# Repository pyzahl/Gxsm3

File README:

General Information
===================

GXSM -- Gnome X Scanning Microscopy: A multi-channel image and
vector-probe data acquisition and visualization system designed for
SPM techniques (STM,AFM..), but also SPA-LEED. A plug-in interface
allows any user add-on data-processing and special hardware and
instrument support.

Based on several hardware options it supports a commercially available
DSP hardware and provided also Open Source Code for all the low level
signal processing tasks and instrument controls in a most flexible and
adaptable manner.

All latest stable software is available
via SVN (gxsm2) and GIT (gxsm3-beta) only

or Live Demo/Install CD:
http://www.ventiotec.de/linux/GXSM-Linux.iso

GXSM Web Site: http://gxsm.sf.net

Installation
============

gxsm3 requires GTK+ >= 3.14.0, GtkSourceView >= 3.14.0, libfftw, libnetcdf, libquicktime
and PyGobject 3.0.x are required to enable python / scripting support.

Simple install procedure:

  % git clone ... gxsm3-src			# checkout / unpack the sources
  % cd gxsm3-src				# change to the toplevel directory
  % ./autogen.sh				# run the `autogen' script
  % make					# build gedit
  [ Become root if necessary ]
  % make install				# install gxsm3

See the file 'INSTALL' for more detailed information.

How to report bugs
==================

Bugs should be reported to the GNOME bug tracking system.
(http://bugzilla.gnome.org, product gedit). You will need to create an
account for yourself.

In the bug report please include:

* Information about your system. For instance:

   - What version of gxsm3
   - What operating system and version
   - What version of the gtk+, glib and gnome libraries

  And anything else you think is relevant.

* How to reproduce the bug. 

* If the bug was a crash, the exact text that was printed out when the
  crash occurred.

* Further information such as stack traces may be useful, but is not
  necessary. If you do send a stack trace, and the error is an X error,
  it will be more useful if the stack trace is produced running the test
  program with the --sync command line option.

Patches
=======

Patches should also be submitted to bugzilla.gnome.org. If the patch
fixes an existing bug, add the patch as an attachment to that bug
report.

Otherwise, enter a new bug report that describes the patch, and attach
the patch to that bug report.

Please create patches with the git format-patch command.

If you are interested in helping us to develop gedit, please see the 
file 'AUTHOR' for contact information and/or send a message to the gedit
mailing list. See also the file 'HACKING' for more detailed information.

  The gxsm team.

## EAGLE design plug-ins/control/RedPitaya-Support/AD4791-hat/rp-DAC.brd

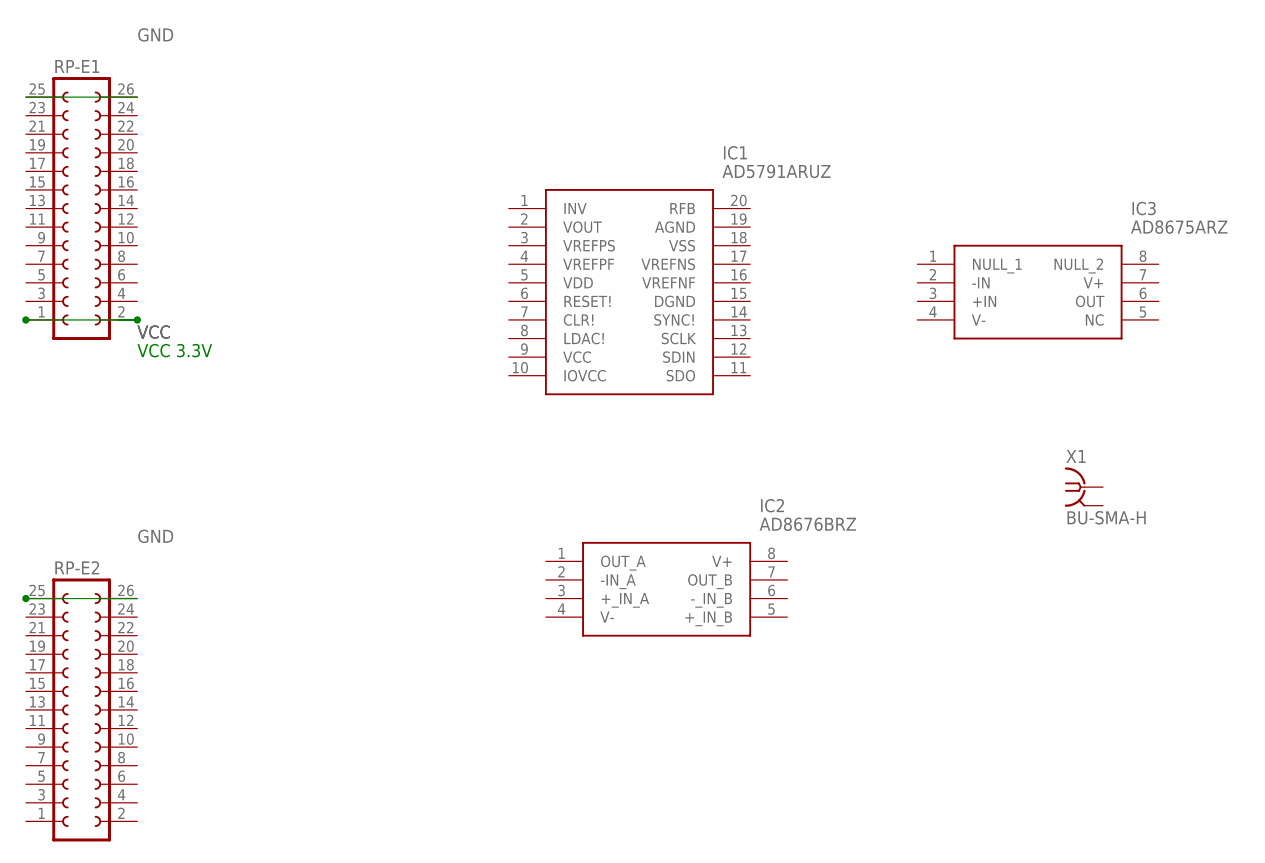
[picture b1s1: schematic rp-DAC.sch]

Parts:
IC1: AD5791ARUZ; SOP65P640X120-20N
IC2: AD8676BRZ; SOIC127P600X175-8N
IC3: AD8675ARZ; SOIC127P600X175-8N
RP-E1, RP-E2: FE13-2
X1: BU-SMA-H

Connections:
GND: RP-E1.25, RP-E1.26, RP-E2.25, RP-E2.26
VCC: RP-E1.1, RP-E1.2

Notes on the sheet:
VCC 3.3V

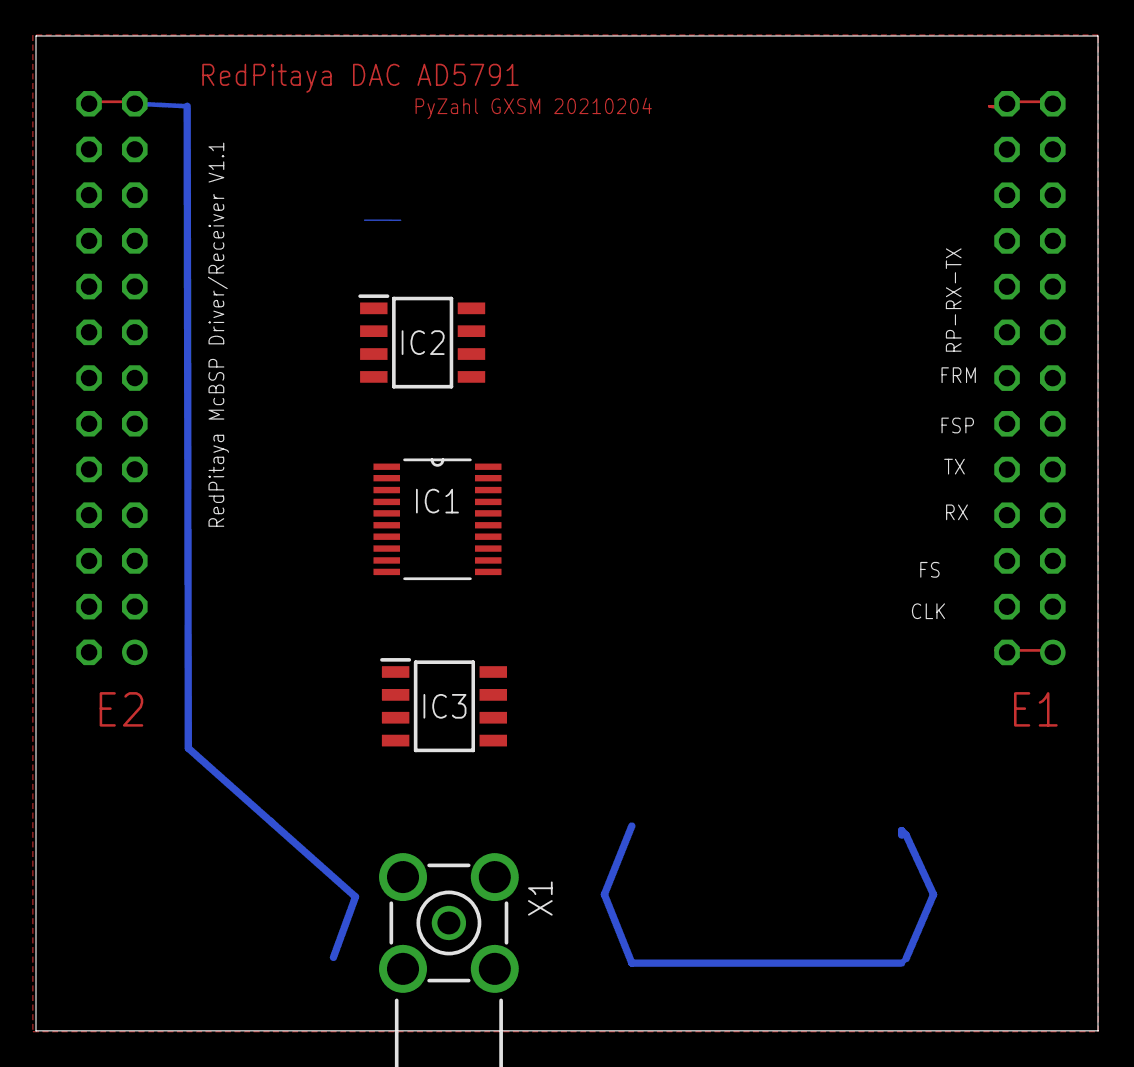
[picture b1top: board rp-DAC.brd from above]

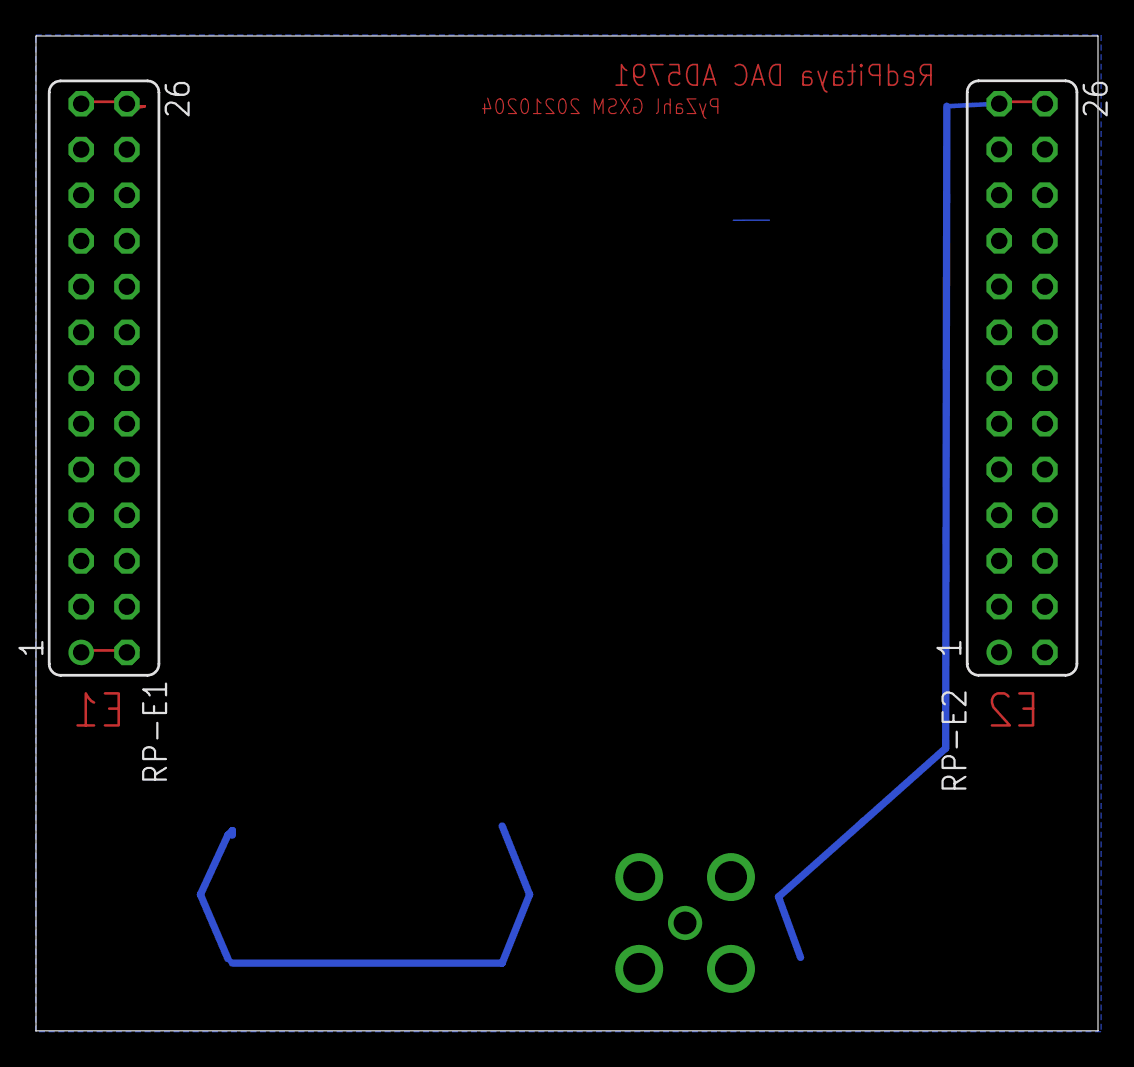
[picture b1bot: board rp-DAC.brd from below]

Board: 2 copper layers, 59.0 x 55.3 mm, 6 parts (2 on the bottom side), 2 nets.

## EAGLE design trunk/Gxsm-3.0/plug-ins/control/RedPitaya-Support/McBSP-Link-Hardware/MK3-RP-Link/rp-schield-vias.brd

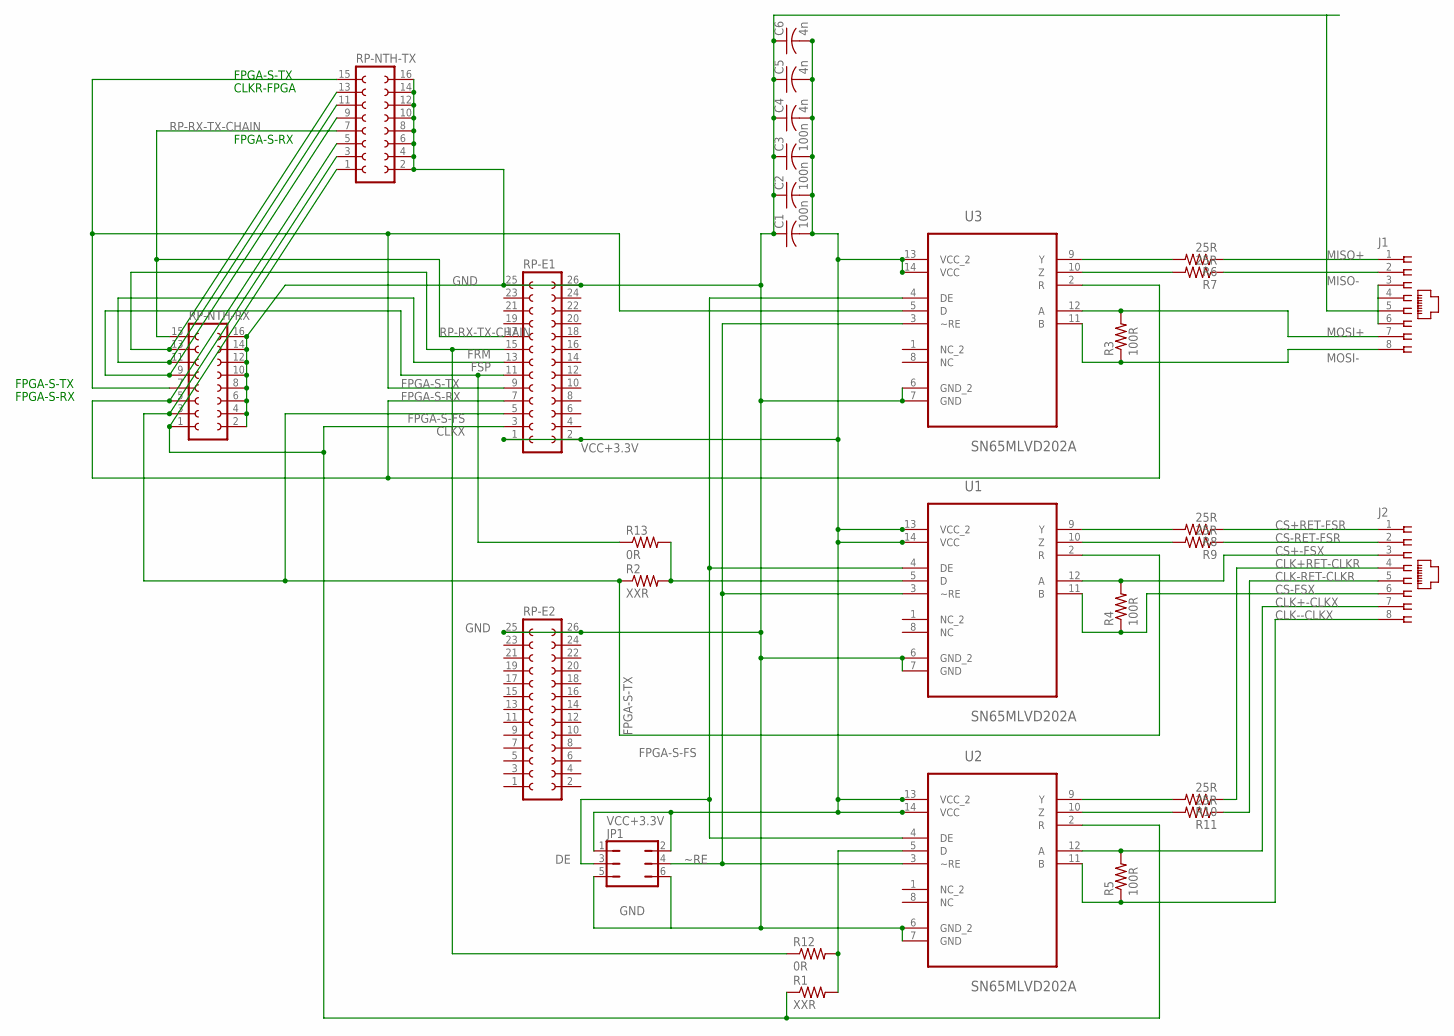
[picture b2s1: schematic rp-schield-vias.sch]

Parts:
C1, C2, C3: 100n; C0805
C4, C5, C6: 4n; C0805
J1, J2: 557785-1-SHIELD; 557785-1
JP1: JP3Q
R1, R2: XXR; M1206
R3, R4, R5: 100R; R0402
R6, R7, R8, R9, R10, R11: 25R; R0402
R12, R13: 0R; M1206
RP-E1, RP-E2: FE13-2
RP-NTH-RX: FE08-2
RP-NTH-TX: FE08-2
U1, U2, U3: SN65MLVD202A; SOIC127P600X175-14N

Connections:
CLK+-CLKX: J2.4, R10.1
CLK+RET-CLKR: J2.7, R5.2, U2.12 (A)
CLK--CLKX: J2.5, R11.1
CLK-RET-CLKR: J2.8, R5.1, U2.11 (B)
CLKX: R1.1, RP-E1.3, RP-NTH-RX.1, RP-NTH-TX.1, U2.2 (R)
CS+-FSX: J2.3, R4.2, U1.12 (A)
CS+RET-FSR: J2.1, R8.1
CS-FSX: J2.6, R4.1, U1.11 (B)
CS-RET-FSR: J2.2, R9.1
DE: JP1.3, U1.4 (DE), U2.4 (DE), U3.4 (DE)
FPGA-S-FS: R2.1, RP-E1.5, RP-NTH-RX.3, RP-NTH-TX.3, U1.2 (R)
FPGA-S-RX: RP-E1.7, RP-NTH-RX.5, RP-NTH-TX.5, U3.2 (R)
FPGA-S-TX: RP-E1.9, RP-NTH-RX.7, RP-NTH-TX.15, U3.5 (D)
FRM: RP-E1.13, RP-NTH-RX.11, RP-NTH-TX.11
FSP: R13.1, RP-E1.11, RP-NTH-RX.9, RP-NTH-TX.9
GND: C1.1, C2.1, C3.1, C4.1, C5.1, C6.1, J1.3, J1.4, J1.5, J1.6, JP1.5, JP1.6, RP-E1.25, RP-E1.26, RP-E2.25, RP-E2.26, RP-NTH-RX.2, RP-NTH-RX.4, RP-NTH-RX.6, RP-NTH-RX.8, RP-NTH-RX.10, RP-NTH-RX.12, RP-NTH-RX.14, RP-NTH-RX.16, RP-NTH-TX.2, RP-NTH-TX.4, RP-NTH-TX.6, RP-NTH-TX.8, RP-NTH-TX.10, RP-NTH-TX.12, RP-NTH-TX.14, RP-NTH-TX.16, U1.6 (GND_2), U1.7 (GND), U2.6 (GND_2), U2.7 (GND), U3.6 (GND_2), U3.7 (GND)
MISO+: J1.1, R6.1
MISO-: J1.2, R7.1
MOSI+: J1.7, R3.2, U3.12 (A)
MOSI-: J1.8, R3.1, U3.11 (B)
unnamed: R6.2, U3.9 (Y)
unnamed: R1.2, R12.2, U2.5 (D)
unnamed: R7.2, U3.10 (Z)
unnamed: R8.2, U1.9 (Y)
unnamed: R9.2, U1.10 (Z)
unnamed: R2.2, R13.2, U1.5 (D)
unnamed: R10.2, U2.9 (Y)
unnamed: R11.2, U2.10 (Z)
unnamed: R12.1, RP-E1.15, RP-NTH-RX.13, RP-NTH-TX.13
RP-RX-TX-CHAIN: RP-E1.17, RP-NTH-RX.15, RP-NTH-TX.7
VCC+3.3V: C1.2, C2.2, C3.2, C4.2, C5.2, C6.2, JP1.1, JP1.2, RP-E1.1, RP-E1.2, U1.13 (VCC_2), U1.14 (VCC), U2.13 (VCC_2), U2.14 (VCC), U3.13 (VCC_2), U3.14 (VCC)
~RE: JP1.4, U1.3 (~RE), U2.3 (~RE), U3.3 (~RE)

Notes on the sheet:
FPGA-S-TX
FPGA-S-RX
CLKR-FPGA

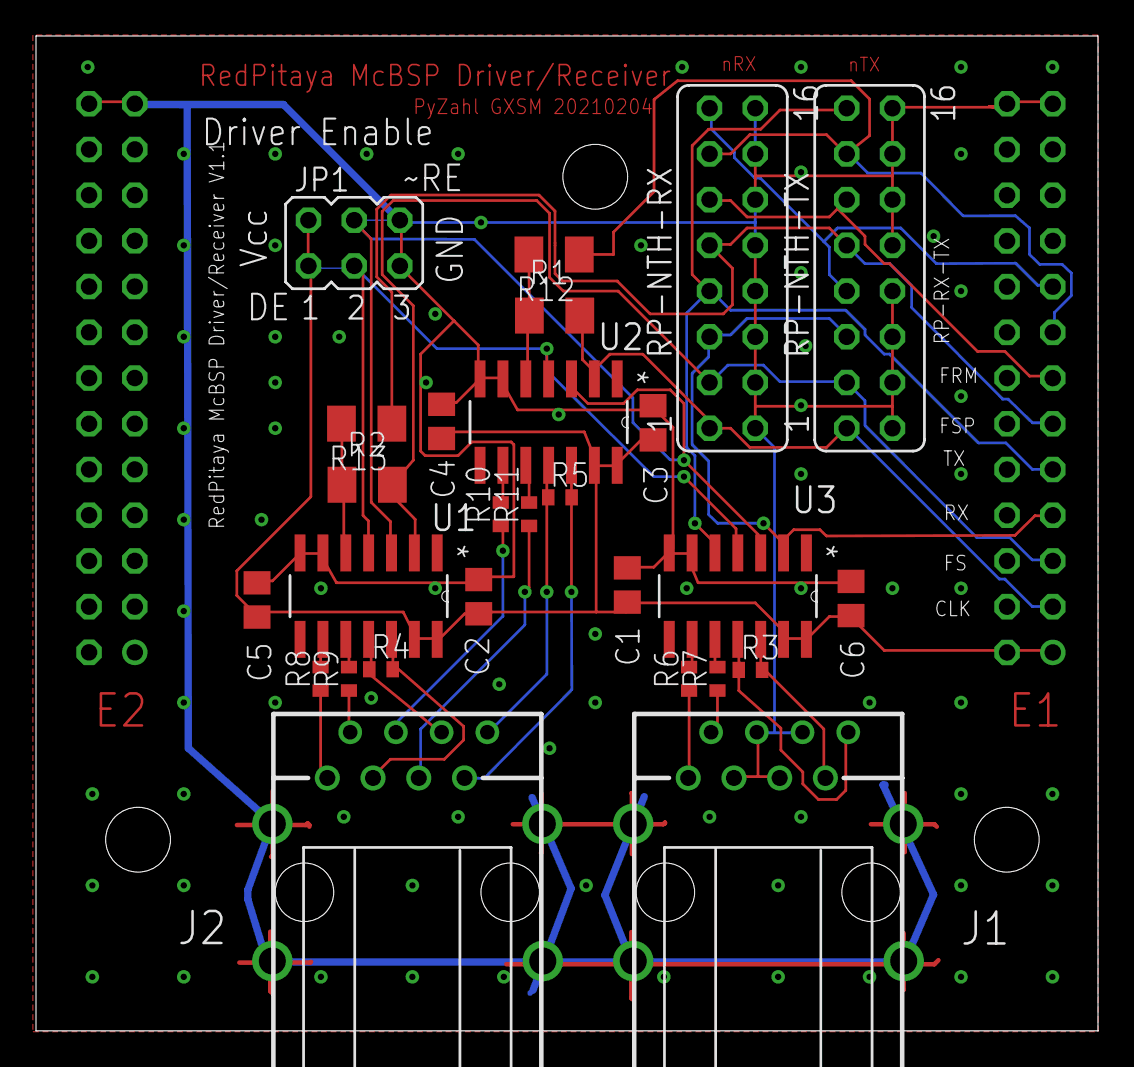
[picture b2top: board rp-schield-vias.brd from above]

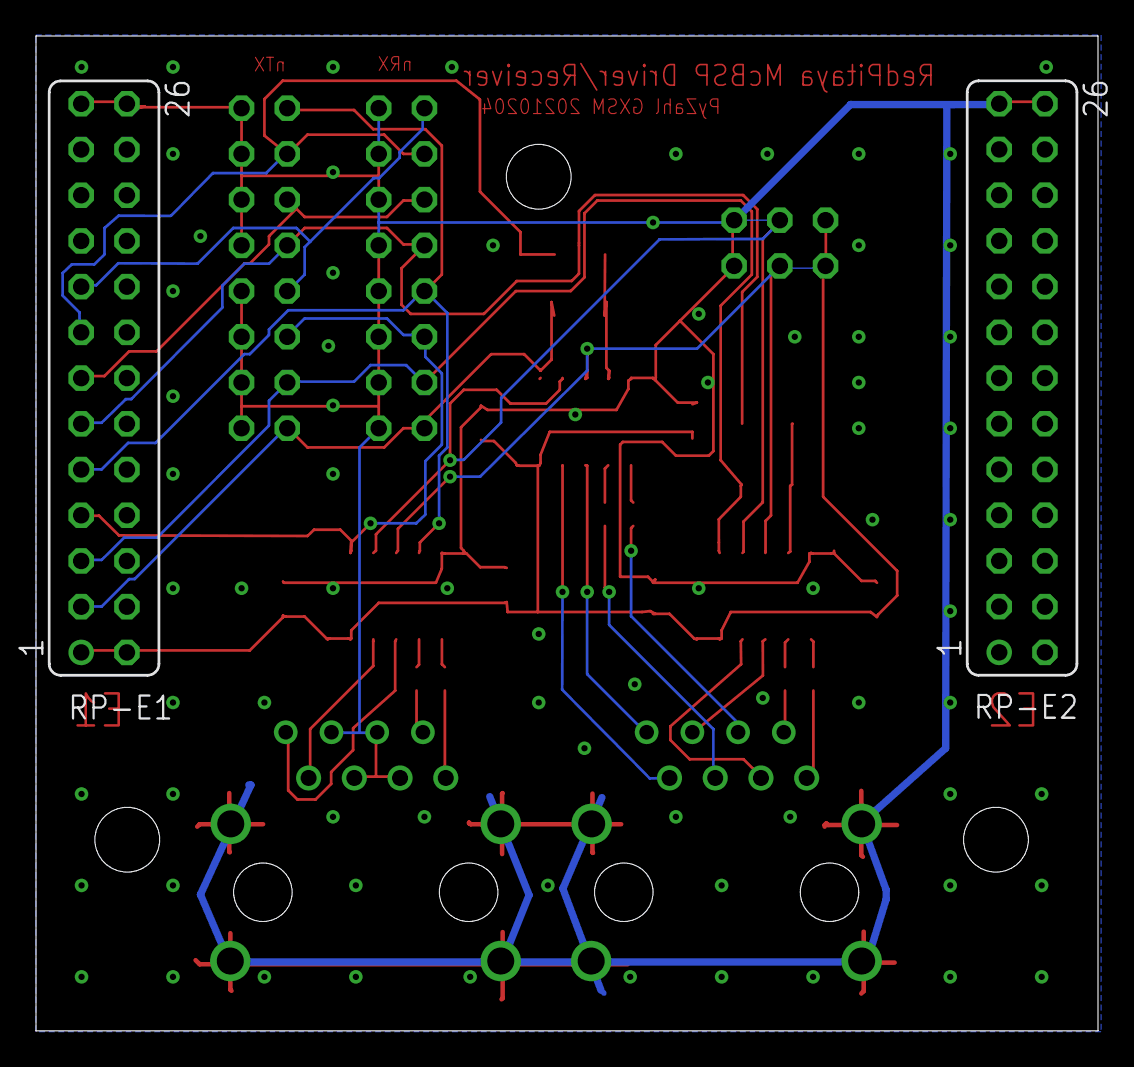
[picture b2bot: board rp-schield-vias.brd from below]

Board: 2 copper layers, 59.0 x 55.3 mm, 29 parts (2 on the bottom side), 32 nets.

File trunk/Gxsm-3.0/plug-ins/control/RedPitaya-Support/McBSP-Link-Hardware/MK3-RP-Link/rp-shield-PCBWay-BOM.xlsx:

Percy Zahl, GXSM RP PACPLL Interface Project |  |  | RP-SHIELD BOM (Bill of Materials) PCB: 60x56mm |  |  | Date: 20210205
Item # | *Designator | *Qty | Manufacturer | *Mfg Part # | Description / Value | *Package/Footprint | Type | Your Instructions / Notes
1 | U1, U2, U3 | 3 | Texas Instruments | SN65MLVD202ADR | SN65MLVD202A Full-duplex M-LVDS transceiver with improved ESD | SOIC127P600X175-14N | SMD
2 | R1, R2 | 2 | Yaego | RC1206FR-0724R9L | RES SMD 24.9 Ohm 1& 1/4W 1206 (or similar) | 1206 | SMD
3 | C1, C2, C3 | 3 | Yageo | CC0805ZRY5V9BB104 | 0.1µF -20%, +80% 50V Ceramic Capacitor Y5V (F) 0805 (or any 100nF CER >35V) | C0805 | SMD
4 | C4, C5, C6 | 3 | Yageo | CC0805KRX7R9BB392 | 3900pF ±10% 50V Ceramic Capacitor X7R 0805 (or any 4nF CER >35V) | C0805 | SMD
5 | J1,J2 | 2 | Amphenol ICC (FCI) | 95672-001LF | Jack Modular Connector 8p8c (RJ45, Ethernet) 90° Angle (Right) Shielded Cat5 | RJ45 8p8c | Through Hole
6 | JP1 | 0 | - | - | 2x3 jumper | - | Through Hole | do not populate (development/testing only)
7 | RP-E1,RP-E2 | 0 | Adafruit Industries LLC | 1979 [1528-1783-ND (DigiKey)] | 2x13 (26pin) RP connector (raspberry pi style stacking header, long) BOTTOM MOU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 | - | Through Hole | do not populate (BOTTOM MOUNT)
8 | RP-NTH-RX | 0 | - | - | header 2x8 | - | Through Hole | do not populate (optional RP interconnect)

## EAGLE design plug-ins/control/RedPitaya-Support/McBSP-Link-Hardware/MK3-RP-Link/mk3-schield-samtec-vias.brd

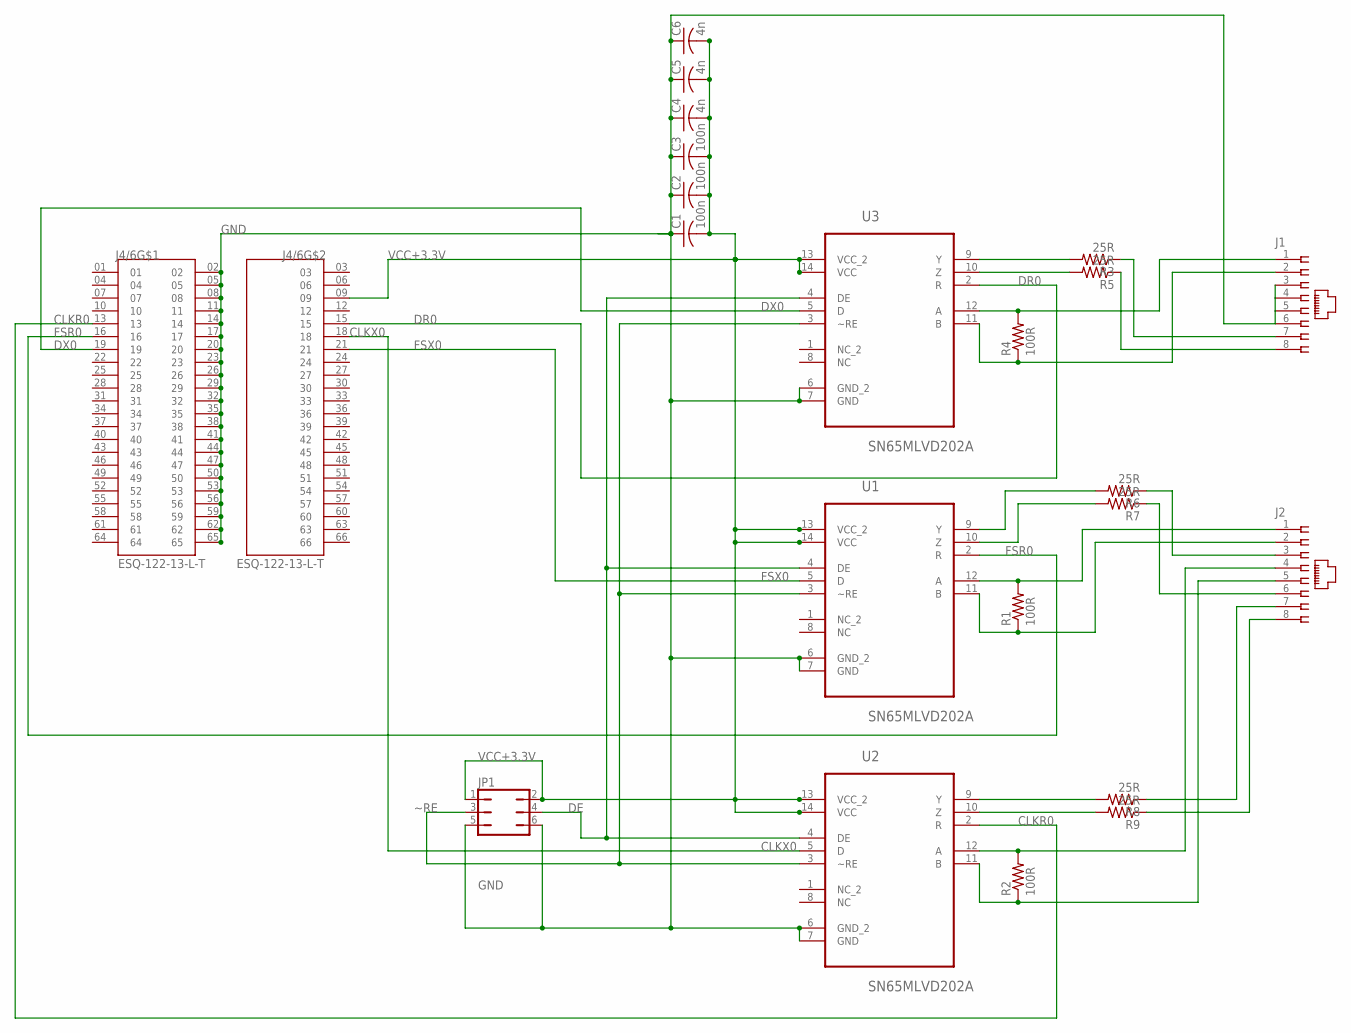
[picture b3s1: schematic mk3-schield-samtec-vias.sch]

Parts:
C1, C2, C3: 100n; C0805
C4, C5, C6: 4n; C0805
J1, J2: 557785-1-SHIELD; 557785-1
J4/6: ESQ-122-13-L-T; SAMTEC_ESQ-122-13-L-T
JP1: JP3Q
R1, R2, R4: 100R; R0402
R3, R5, R6, R7, R8, R9: 25R; R0402
U1, U2, U3: SN65MLVD202A; SOIC127P600X175-14N

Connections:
CLKR0: J4/6.13, U2.2 (R)
CLKX0: J4/6.18, U2.5 (D)
DE: JP1.4, U1.4 (DE), U2.4 (DE), U3.4 (DE)
DR0: J4/6.15, U3.2 (R)
DX0: J4/6.19, U3.5 (D)
FSR0: J4/6.16, U1.2 (R)
FSX0: J4/6.21, U1.5 (D)
GND: C1.1, C2.1, C3.1, C4.1, C5.1, C6.1, J1.3, J1.4, J1.5, J1.6, J4/6.02, J4/6.05, J4/6.08, J4/6.11, J4/6.14, J4/6.17, J4/6.20, J4/6.23, J4/6.26, J4/6.29, J4/6.32, J4/6.35, J4/6.38, J4/6.41, J4/6.44, J4/6.47, J4/6.50, J4/6.53, J4/6.56, J4/6.59, J4/6.62, J4/6.65, JP1.5, JP1.6, U1.6 (GND_2), U1.7 (GND), U2.6 (GND_2), U2.7 (GND), U3.6 (GND_2), U3.7 (GND)
unnamed: J1.1, R4.2, U3.12 (A)
unnamed: J1.2, R4.1, U3.11 (B)
unnamed: J1.7, R3.1
unnamed: J1.8, R5.1
unnamed: J2.1, R1.2, U1.12 (A)
unnamed: J2.2, R1.1, U1.11 (B)
unnamed: J2.3, R6.1
unnamed: J2.6, R7.1
unnamed: J2.4, R2.2, U2.12 (A)
unnamed: J2.5, R2.1, U2.11 (B)
unnamed: J2.7, R8.1
unnamed: J2.8, R9.1
unnamed: R3.2, U3.9 (Y)
unnamed: R5.2, U3.10 (Z)
unnamed: R6.2, U1.9 (Y)
unnamed: R7.2, U1.10 (Z)
unnamed: R8.2, U2.9 (Y)
unnamed: R9.2, U2.10 (Z)
VCC+3.3V: C1.2, C2.2, C3.2, C4.2, C5.2, C6.2, J4/6.09, JP1.1, JP1.2, U1.13 (VCC_2), U1.14 (VCC), U2.13 (VCC_2), U2.14 (VCC), U3.13 (VCC_2), U3.14 (VCC)
~RE: JP1.3, U1.3 (~RE), U2.3 (~RE), U3.3 (~RE)

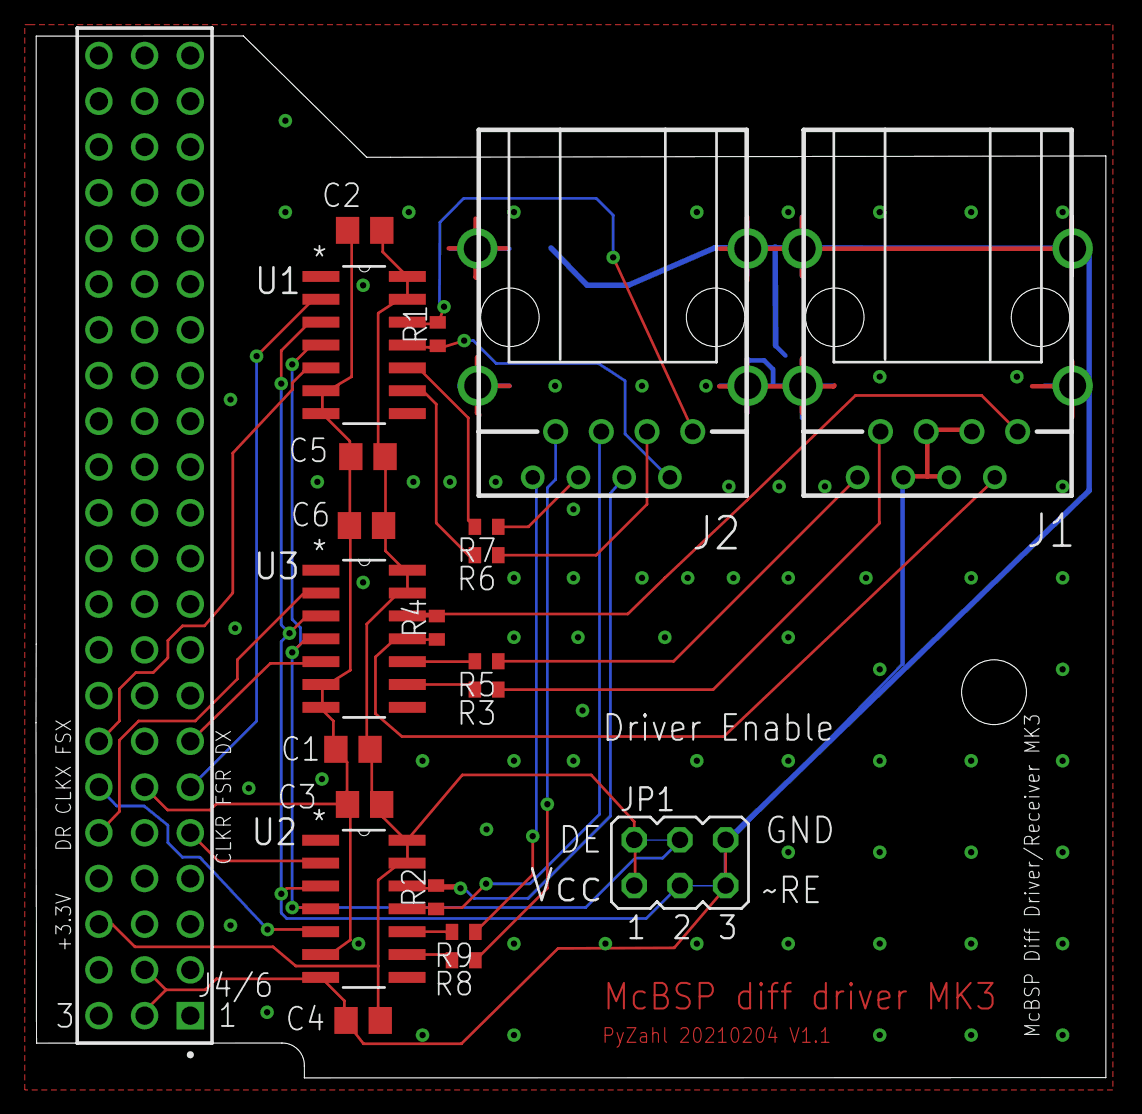
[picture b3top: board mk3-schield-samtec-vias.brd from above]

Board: 2 copper layers, 59.4 x 57.9 mm, 22 parts (0 on the bottom side), 28 nets.

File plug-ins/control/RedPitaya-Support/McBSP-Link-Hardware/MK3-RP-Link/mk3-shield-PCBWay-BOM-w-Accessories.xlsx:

Percy Zahl, GXSM RP PACPLL Interface Project |  |  | MK3-SHIELD BOM (Bill of Materials) PCB: 60x52mm |  |  | Date: 20210205
Item # | *Designator | *Qty | Manufacturer | *Mfg Part # | Description / Value | *Package/Footprint | Type | Your Instructions / Notes
1 | U1, U2, U3 | 3 | Texas Instruments | SN65MLVD202ADR | SN65MLVD202A Full-duplex M-LVDS transceiver with improved ESD | SOIC127P600X175-14N | SMD
2 | C1, C2, C3 | 3 | Yageo | CC0805ZRY5V9BB104 | 0.1µF -20%, +80% 50V Ceramic Capacitor Y5V (F) 0805 (or any 100nF CER >35V) | C0805 | SMD
3 | C4, C5, C6 | 3 | Yageo | CC0805KRX7R9BB392 | 3900pF ±10% 50V Ceramic Capacitor X7R 0805 (or any 4nF CER >35V) | C0805 | SMD
4 | J1,J2 | 2 | Amphenol ICC (FCI) | 95672-001LF | Jack Modular Connector 8p8c (RJ45, Ethernet) 90° Angle (Right) Shielded Cat5 | RJ45 8p8c | Through Hole
5 | JP1 | 0 | - | - | 2x3 jumper | - | Through Hole | do not populate (development/testing only)
6 | JP4/6 | 2 | SamTec | ESQ-122-13-L-T | 3row 44pos in two 2x 3x22 ESQ-122-13-L-T stacking board inter connect |  | Through Hole | do not populate
 |  |  | MK3-SHIELD and RP connection accessories
 |  | 2 | HellermannTyton | PCRED5, PCFEL5 | CAT5 Ethernet CABLE MOD 8P8C Plug-Plug 5ft (Red, Yellow) – may use a shielded c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 |  |  | suggested cable set and length for MK3 – RP link cable. Longer works, may limit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
 |  | 2 | Adafruit industries sLLC | 909 [1528-1572-ND (DigiKey)] | Modular Cable Jack to Plug 8p8c (RJ45, Ethernet) 0.98' (300.0mm) |  |  | for MK3 internal wiring to rear panel
 | JP4/6 | 2 | SamTec | ESQ-122-13-L-T | 3row 44pos in two 2x 3x22 ESQ-122-13-L-T stacking board inter connect |  |  | cut pins CLKR0, DR0, FSR0 !!! Should NOT connect to A810.

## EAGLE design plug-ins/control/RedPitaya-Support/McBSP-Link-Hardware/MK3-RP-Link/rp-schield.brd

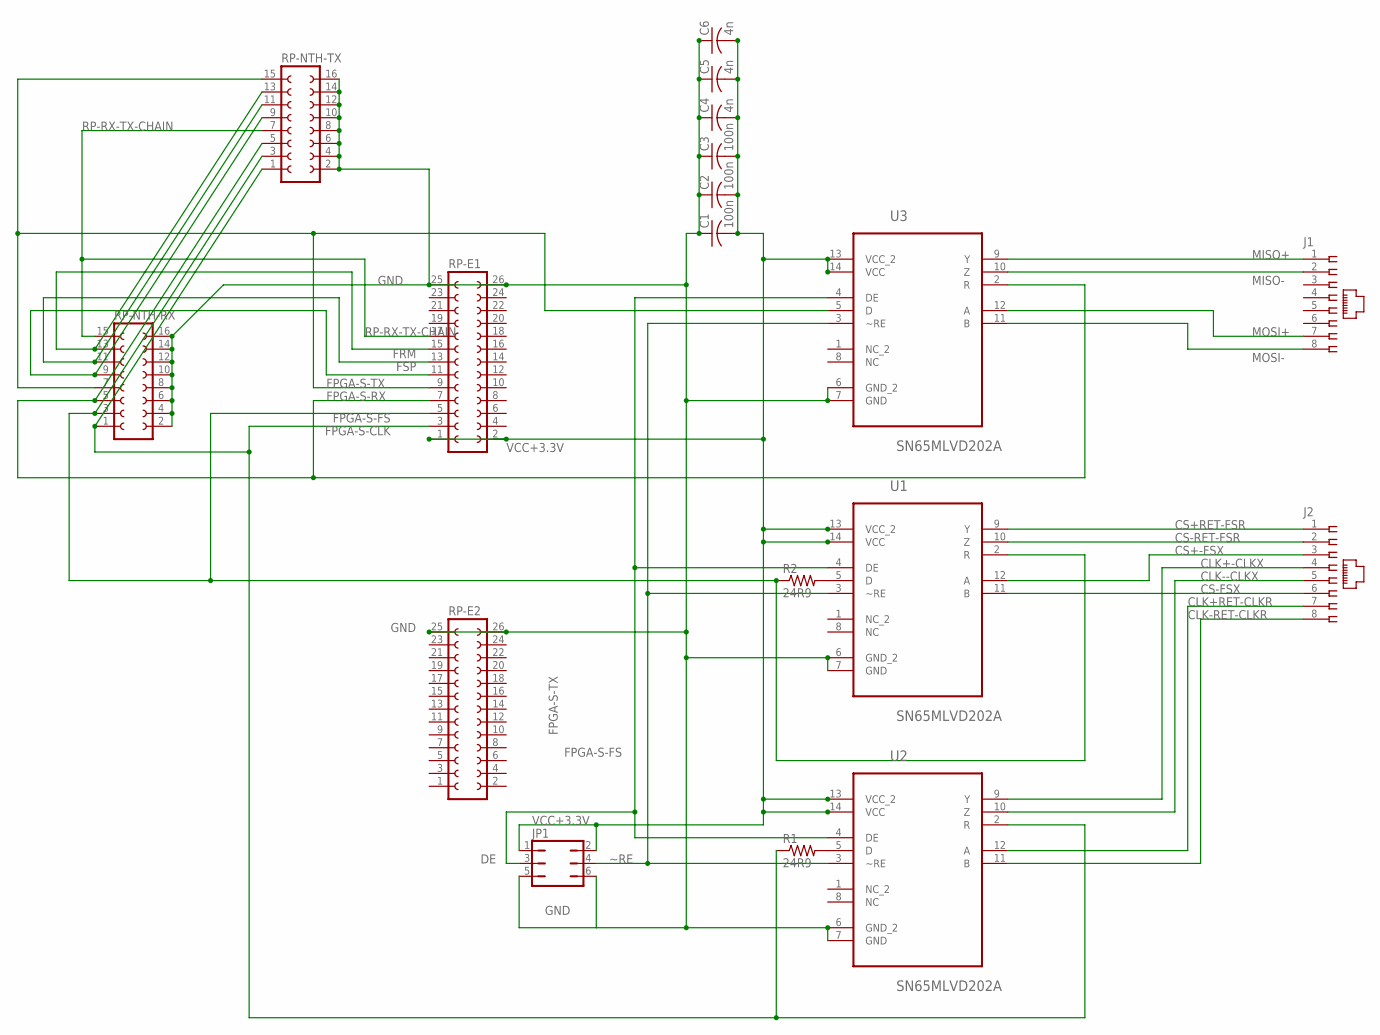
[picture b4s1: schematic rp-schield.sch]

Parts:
C1, C2, C3: 100n; C0805
C4, C5, C6: 4n; C0805
J1, J2: 557785-1-SHIELD; 557785-1
JP1: JP3Q
R1, R2: 24R9; M1206
RP-E1, RP-E2: FE13-2
RP-NTH-RX: FE08-2
RP-NTH-TX: FE08-2
U1, U2, U3: SN65MLVD202A; SOIC127P600X175-14N

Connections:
CLK+-CLKX: J2.4, U2.9 (Y)
CLK+RET-CLKR: J2.7, U2.12 (A)
CLK--CLKX: J2.5, U2.10 (Z)
CLK-RET-CLKR: J2.8, U2.11 (B)
CS+-FSX: J2.3, U1.12 (A)
CS+RET-FSR: J2.1, U1.9 (Y)
CS-FSX: J2.6, U1.11 (B)
CS-RET-FSR: J2.2, U1.10 (Z)
DE: JP1.3, U1.4 (DE), U2.4 (DE), U3.4 (DE)
FPGA-S-CLK: R1.1, RP-E1.3, RP-NTH-RX.1, RP-NTH-TX.1, U2.2 (R)
FPGA-S-FS: R2.1, RP-E1.5, RP-NTH-RX.3, RP-NTH-TX.3, U1.2 (R)
FPGA-S-RX: RP-E1.7, RP-NTH-RX.5, RP-NTH-TX.5, U3.2 (R)
FPGA-S-TX: RP-E1.9, RP-NTH-RX.7, RP-NTH-TX.15, U3.5 (D)
FRM: RP-E1.13, RP-NTH-RX.11, RP-NTH-TX.11
FSP: RP-E1.11, RP-NTH-RX.9, RP-NTH-TX.9
GND: C1.1, C2.1, C3.1, C4.1, C5.1, C6.1, J1.3, J1.4, J1.5, J1.6, JP1.5, JP1.6, RP-E1.25, RP-E1.26, RP-E2.25, RP-E2.26, RP-NTH-RX.2, RP-NTH-RX.4, RP-NTH-RX.6, RP-NTH-RX.8, RP-NTH-RX.10, RP-NTH-RX.12, RP-NTH-RX.14, RP-NTH-RX.16, RP-NTH-TX.2, RP-NTH-TX.4, RP-NTH-TX.6, RP-NTH-TX.8, RP-NTH-TX.10, RP-NTH-TX.12, RP-NTH-TX.14, RP-NTH-TX.16, U1.6 (GND_2), U1.7 (GND), U2.6 (GND_2), U2.7 (GND), U3.6 (GND_2), U3.7 (GND)
MISO+: J1.1, U3.9 (Y)
MISO-: J1.2, U3.10 (Z)
MOSI+: J1.7, U3.12 (A)
MOSI-: J1.8, U3.11 (B)
unnamed: R1.2, U2.5 (D)
unnamed: R2.2, U1.5 (D)
unnamed: RP-E1.15, RP-NTH-RX.13, RP-NTH-TX.13
RP-RX-TX-CHAIN: RP-E1.17, RP-NTH-RX.15, RP-NTH-TX.7
VCC+3.3V: C1.2, C2.2, C3.2, C4.2, C5.2, C6.2, JP1.1, JP1.2, RP-E1.1, RP-E1.2, U1.13 (VCC_2), U1.14 (VCC), U2.13 (VCC_2), U2.14 (VCC), U3.13 (VCC_2), U3.14 (VCC)
~RE: JP1.4, U1.3 (~RE), U2.3 (~RE), U3.3 (~RE)

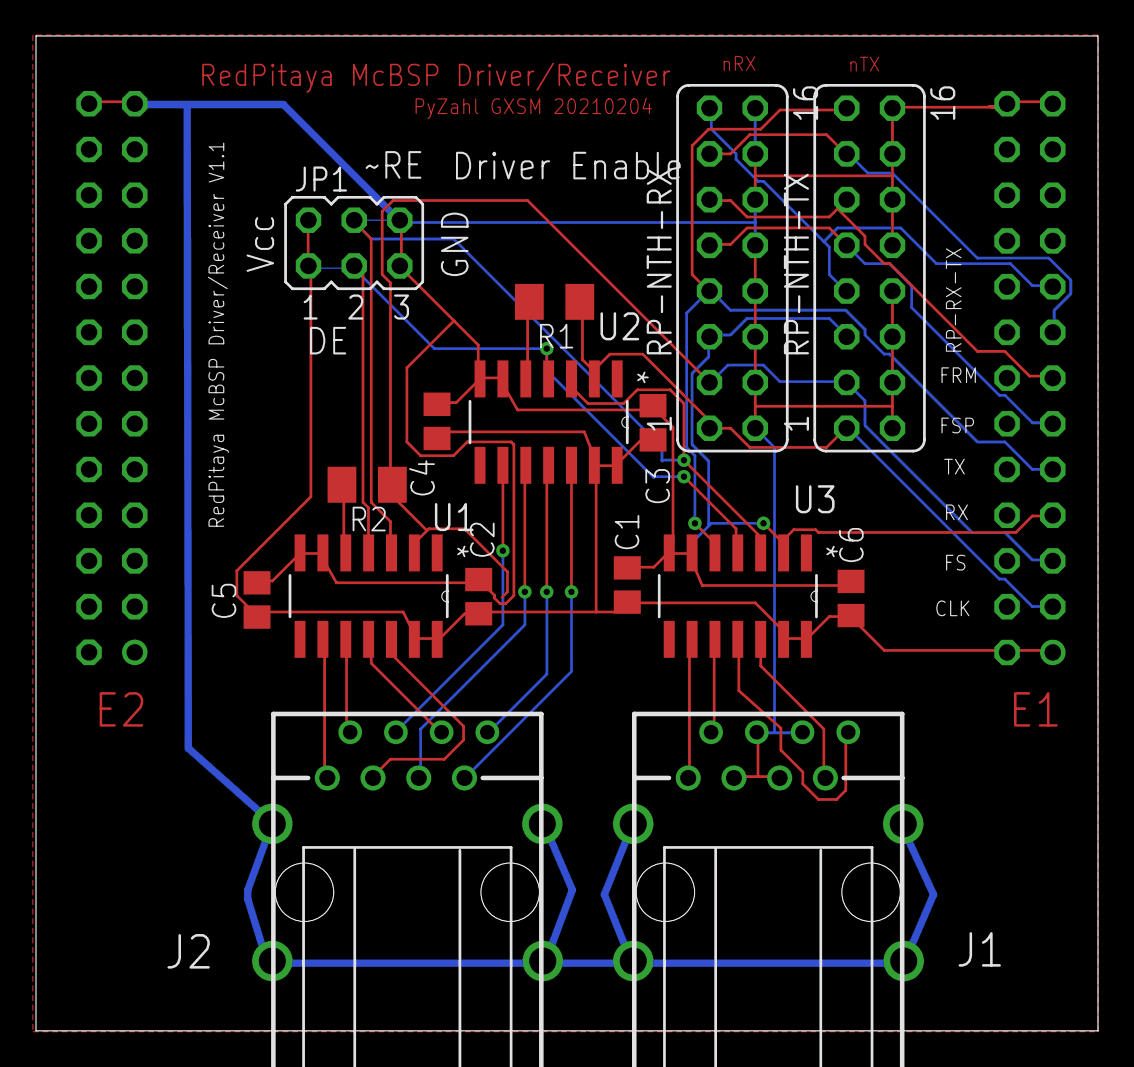
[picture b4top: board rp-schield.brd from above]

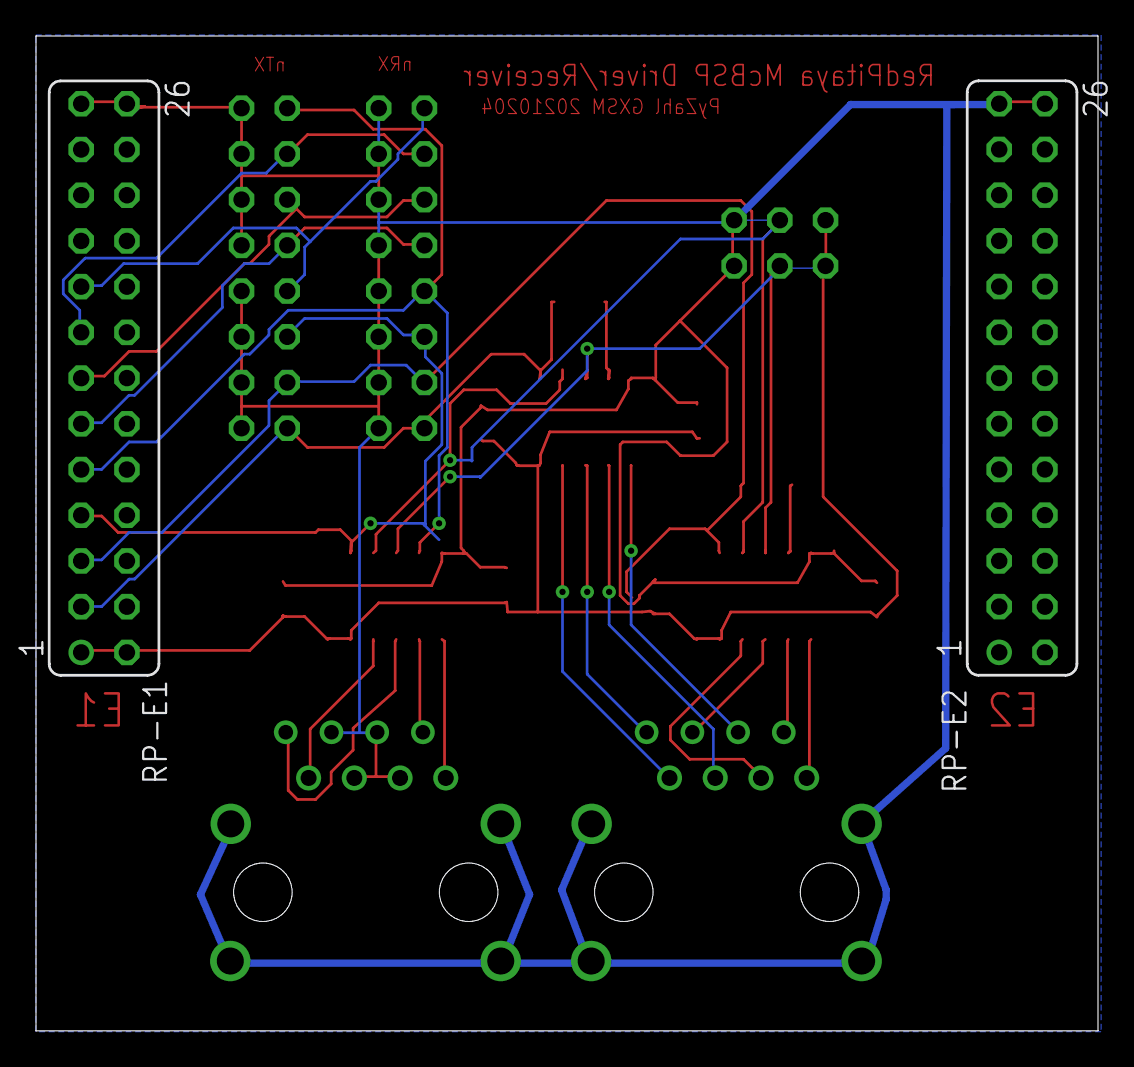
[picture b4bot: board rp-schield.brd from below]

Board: 2 copper layers, 59.0 x 55.3 mm, 18 parts (2 on the bottom side), 26 nets.

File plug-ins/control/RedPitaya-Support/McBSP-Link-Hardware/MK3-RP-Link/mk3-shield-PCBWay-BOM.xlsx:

Percy Zahl, GXSM RP PACPLL Interface Project |  |  | MK3-SHIELD BOM (Bill of Materials) PCB: 60x60mm |  |  | Date: 20210205
Item # | *Designator | *Qty | Manufacturer | *Mfg Part # | Description / Value | *Package/Footprint | Type | Your Instructions / Notes
1 | U1, U2, U3 | 3 | Texas Instruments | SN65MLVD202ADR | SN65MLVD202A Full-duplex M-LVDS transceiver with improved ESD | SOIC127P600X175-14N | SMD
2 | C1, C2, C3 | 3 | Yageo | CC0805ZRY5V9BB104 | 0.1µF -20%, +80% 50V Ceramic Capacitor Y5V (F) 0805 (or any 100nF CER >35V) | C0805 | SMD
3 | C4, C5, C6 | 3 | Yageo | CC0805KRX7R9BB392 | 3900pF ±10% 50V Ceramic Capacitor X7R 0805 (or any 4nF CER >35V) | C0805 | SMD
4 | J1,J2 | 2 | Amphenol ICC (FCI) | 95672-001LF | Jack Modular Connector 8p8c (RJ45, Ethernet) 90° Angle (Right) Shielded Cat5 | RJ45 8p8c | Through Hole
5** | JP1 | 0 | - | - | 2x3 jumper | - | Through Hole | do not populate (development/testing only)
6** | JP4/6 | 0 | SamTec | ESQ-122-13-L-T | 3row 44pos in two 2x 3x22 ESQ-122-13-L-T stacking board inter connect |  | Through Hole | do not populate (bottom side mount!!)
** | DO NOT ORDER, INCLUDE AND INSTALL!!!
